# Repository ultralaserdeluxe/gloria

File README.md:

gloria
======

TSEA29: Lagerrobot

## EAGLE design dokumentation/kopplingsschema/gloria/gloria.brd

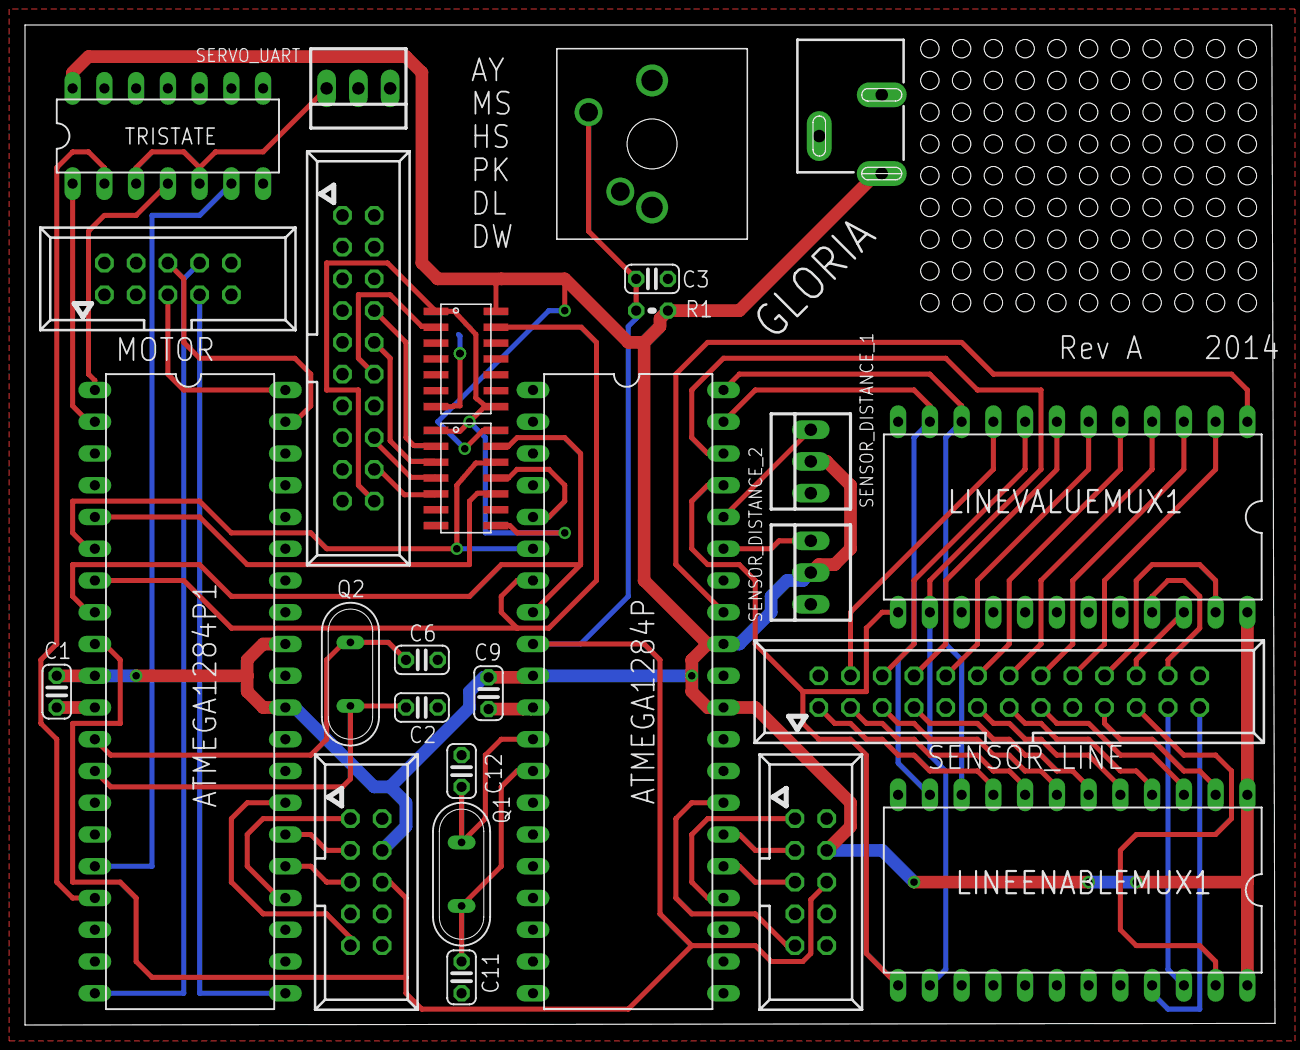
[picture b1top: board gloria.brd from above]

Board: 2 copper layers, 100.0 x 80.0 mm, 36 parts (0 on the bottom side), 64 nets.

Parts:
ATMEGA1284P: SENSOR UNIT; DIL40
ATMEGA1284P1: DRIVE UNIT; DIL40
C1, C3, C9: 100n; C025-024X044
C2, C6, C11, C12: 22p; C025-024X044
JP1: POWER_JACKSLT; POWER_JACK_SLOT
JP26, JP27, JP28, JP29, JP30, JP31, JP32, JP33, JP34: M11POGOPIN_HOLES_ONLY; 1X11_HOLES_ONLY
JTAG_SEN: 057-010-1
JTAG_STYR: 057-010-1
LINEENABLEMUX1: 4067N; DIL24-6
LINEVALUEMUX1: 4067N; DIL24-6
MOTOR: 057-010-1
Q1, Q2: 16M; QS
R1: 10k; 0204V
SENSOR_DISTANCE_1, SENSOR_DISTANCE_2: 22-23-2031
SENSOR_LINE: 057-026-1
SERVO_UART: 22-23-2031
TRISTATE: 74LS125N; DIL14
U$1, U$2: TXB0104SOIC(D); TXB0104
U$6: CHERRY-MX-I
X: 057-020-1

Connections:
DISTANCELEFT: ATMEGA1284P.36, SENSOR_DISTANCE_1.3
GND: ATMEGA1284P.11, ATMEGA1284P.31, ATMEGA1284P1.11, ATMEGA1284P1.31, C1.1, C2.1, C3.1, C6.1, C9.1, C11.1, C12.1, JP1.GND@1, JP1.GND@2, JTAG_SEN.2, JTAG_SEN.10, JTAG_STYR.2, JTAG_STYR.10, LINEENABLEMUX1.12, LINEENABLEMUX1.15, LINEVALUEMUX1.12, LINEVALUEMUX1.15, MOTOR.1, SENSOR_DISTANCE_1.1, SENSOR_DISTANCE_2.1, SENSOR_LINE.2, SENSOR_LINE.9, SENSOR_LINE.17, SENSOR_LINE.26, SERVO_UART.1, TRISTATE.7, U$1.P$7, U$2.P$7, U$6.PIN-1, X.2
LINEADDR0: ATMEGA1284P.40, LINEENABLEMUX1.10, LINEVALUEMUX1.10
LINEADDR1: ATMEGA1284P.39, LINEENABLEMUX1.11, LINEVALUEMUX1.11
LINEADDR2: ATMEGA1284P.38, LINEENABLEMUX1.14, LINEVALUEMUX1.14
LINEADDR3: ATMEGA1284P.37, LINEENABLEMUX1.13, LINEVALUEMUX1.13
LINEVALUE: ATMEGA1284P.33, LINEVALUEMUX1.1
MISO: ATMEGA1284P.7, ATMEGA1284P1.7, U$2.P$13
MOSI: ATMEGA1284P.6, ATMEGA1284P1.6, U$1.P$12
unnamed: ATMEGA1284P.27, JTAG_SEN.9
unnamed: ATMEGA1284P1.24, JTAG_STYR.1
unnamed: ATMEGA1284P.26, JTAG_SEN.3
unnamed: ATMEGA1284P.25, JTAG_SEN.5
unnamed: ATMEGA1284P.24, JTAG_SEN.1
unnamed: ATMEGA1284P1.27, JTAG_STYR.9
unnamed: ATMEGA1284P1.26, JTAG_STYR.3
unnamed: ATMEGA1284P1.25, JTAG_STYR.5
unnamed: ATMEGA1284P1.21, MOTOR.7
unnamed: LINEENABLEMUX1.9, SENSOR_LINE.1
unnamed: LINEENABLEMUX1.8, SENSOR_LINE.3
unnamed: LINEENABLEMUX1.7, SENSOR_LINE.5
unnamed: LINEENABLEMUX1.6, SENSOR_LINE.7
unnamed: LINEENABLEMUX1.5, SENSOR_LINE.11
unnamed: LINEENABLEMUX1.4, SENSOR_LINE.13
unnamed: LINEENABLEMUX1.3, SENSOR_LINE.15
unnamed: LINEENABLEMUX1.2, SENSOR_LINE.19
unnamed: LINEENABLEMUX1.23, SENSOR_LINE.21
unnamed: LINEENABLEMUX1.22, SENSOR_LINE.23
unnamed: LINEENABLEMUX1.21, SENSOR_LINE.25
unnamed: LINEVALUEMUX1.9, SENSOR_LINE.4
unnamed: LINEVALUEMUX1.8, SENSOR_LINE.6
unnamed: LINEVALUEMUX1.7, SENSOR_LINE.8
unnamed: LINEVALUEMUX1.6, SENSOR_LINE.10
unnamed: LINEVALUEMUX1.5, SENSOR_LINE.12
unnamed: LINEVALUEMUX1.4, SENSOR_LINE.14
unnamed: LINEVALUEMUX1.3, SENSOR_LINE.16
unnamed: LINEVALUEMUX1.2, SENSOR_LINE.18
unnamed: LINEVALUEMUX1.23, SENSOR_LINE.20
unnamed: LINEVALUEMUX1.22, SENSOR_LINE.22
unnamed: LINEVALUEMUX1.21, SENSOR_LINE.24
unnamed: ATMEGA1284P.35, SENSOR_DISTANCE_2.3
unnamed: U$1.P$1, U$1.P$8, U$2.P$1, U$2.P$8, X.20
unnamed: ATMEGA1284P1.40, MOTOR.5
unnamed: U$1.P$2, X.8
unnamed: U$1.P$3, X.10
unnamed: U$2.P$2, X.12
unnamed: U$1.P$4, X.16
unnamed: U$1.P$5, X.18
unnamed: ATMEGA1284P1.39, MOTOR.6
unnamed: ATMEGA1284P.12, C12.2, Q1.2
unnamed: ATMEGA1284P1.20, MOTOR.8
unnamed: ATMEGA1284P.13, C11.2, Q1.1
unnamed: ATMEGA1284P1.12, C6.2, Q2.2
unnamed: ATMEGA1284P1.13, C2.2, Q2.1
RESET: ATMEGA1284P.9, ATMEGA1284P1.9, C3.2, JTAG_SEN.6, JTAG_STYR.6, R1.1, U$6.PIN-2
SCK: ATMEGA1284P.8, ATMEGA1284P1.8, U$1.P$13
SERVOUART: SERVO_UART.3, TRISTATE.3, TRISTATE.5
SS0: ATMEGA1284P1.5, U$1.P$10
SS1: ATMEGA1284P.5, U$1.P$11
STYR_UART_RX_E: ATMEGA1284P1.1, TRISTATE.4
STYR_UART_TX_E: ATMEGA1284P1.2, TRISTATE.1
UART1RX: ATMEGA1284P1.16, TRISTATE.6
UART1TX: ATMEGA1284P1.17, TRISTATE.2
VCC: ATMEGA1284P.10, ATMEGA1284P.30, ATMEGA1284P.32, ATMEGA1284P1.10, ATMEGA1284P1.30, ATMEGA1284P1.32, C1.2, C9.2, JP1.PWR, JTAG_SEN.4, JTAG_STYR.4, LINEENABLEMUX1.1, LINEENABLEMUX1.24, LINEVALUEMUX1.24, R1.2, SENSOR_DISTANCE_1.2, SENSOR_DISTANCE_2.2, TRISTATE.14, U$1.P$14, U$2.P$14

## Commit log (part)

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2014-10-29 Modified is_on_straight.
2014-10-29 Fixed distance values
2014-10-29 Changed regulator behaviour when on crossings or breaks.
2014-10-29 Fixed station_center on crossings/breaks.
2014-10-29 Added setAll function.
2014-10-29 Changed station front for the better and the lower/upper limits.
2014-10-29 Changed stuff.
2014-10-29 driveUnit can now handle float in motor speeds.
2014-10-29 pcThread can now work with the shared stuff dictionary.
2014-10-29 Lots of changes.
2014-10-29 Changed station functions to a class and made it incorporate past values in desicions.
2014-10-29 Added hasPackage functionality.
2014-10-29 Fixed regulator.
2014-10-29 Fixed stop stations.
2014-10-29 stopstations works
2014-11-03 Fixed broken file.
2014-11-03 Designspec updated to v1.0(unconfirmed)
2014-11-03 uppdaterat statusrapporten
2014-11-04 gitignore updated w Atmes Studio, styrenhet src initiated
2014-11-04 uppdaterat datum i statusrapport
2014-11-06 gitignore updated, initiated src styrenhet and sensorenhet
2014-11-06 Kodstandard added
2014-11-06 Added a file for SPI functions.
2014-11-06 Created a simple echo test with SPI interrupts.
2014-11-07 Protokoll möte 20141105 updated
2014-11-07 Added PythonModule for PC and DAD
2014-11-08 Built data-types and queue for styrenhet
2014-11-09 Styrenhet now builds
2014-11-09 Added ISR to spi functions.
2014-11-09 Styrenhet partially updated
2014-11-09 Implemented transmission for SPI slave, untested
2014-11-10 Testing PWM.
2014-11-10 Removed bogus comments
2014-11-10 Mötesprotokoll 20141110 added
2014-11-11 Removed bogus comments from PCmodule
2014-11-11 kopplingsschema updated
2014-11-11 Update gitignore w eagle
2014-11-12 PCGUI stub
2014-11-12 Test textfile added
2014-11-12 Experimenting with .txt file command sending
2014-11-12 Working GUI for motor handling!
2014-11-12 loleagle
2014-11-12 wrote a new pc-dad communication module
2014-11-13 added styrlogik
2014-11-13 Improved performance sensorenhet
2014-11-14 Fixed usart.
2014-11-14 Test of controlling servii.
2014-11-14 Added functions for working with sensors.
2014-11-14 Updated sensor unit to use the new sensor functions.
2014-11-15 Restructured and updated styrenhet. SPI not implemented.
2014-11-15 some stuff changed in styrlogik
2014-11-15 moved styrlogik to martins
2014-11-15 Styrmodul hopefully has functional datatypes
2014-11-15 Added Mötesprotokoll 20141115
2014-11-16 Changed spi functions to not use the transmit queue.
2014-11-16 Fixed uninitialised pointer.
2014-11-16 Added working spi recieve handler and updated main loop.
2014-11-16 Styrenhet now acts based on streams of data
2014-11-17 new module for sensorreading
2014-11-17 Various updates
2014-11-18 flyttade mainthreadtill styrlogik, började på kalibreringsfunktionen
2014-11-18 wrote an arm class
2014-11-19 kalibrering klar? började på styrbibliotek för maintråden
2014-11-19 Styrenhet updated. Theres code to fix memoryleak (gets stuck in loop) and updated servo_init (still not working properly)
2014-11-20 Cleaned folder of unusable files, made copy, cont. GUI
2014-11-20 Added GUI input for ARM, working on autoarm/motor, also status/calibrate
2014-11-20 Fully working GUI for old version
2014-11-20 la till lite grejjer i driveunit å i maintraden
2014-11-20 updated statusrapport
2014-11-20 new joystick class and a testprogram to controll motors with joystick
2014-11-21 Cleaned naming errors of modules, SPI module missing, where is it?
2014-11-21 removed martin folder
2014-11-21 moved some python files around, everything for the pc is under PC and everything for the mainunit is under huvudenhet
2014-11-21 added some missing files in styrlogik
2014-11-21 changed beaglemain
2014-11-21 Mötesprotokoll 20141121 added
2014-11-21 Added motor control.
2014-11-21 fixed checksubelement so it handles float
2014-11-21 Fixed motor control.
2014-11-22 fixed pcModule with package tail handling
2014-11-22 Updated circuit diagram.
2014-11-23 Various changes
2014-11-23 Fixed a few input bugs resulting in nonexisting values
2014-11-23 Updated circuit diagrams.
2014-11-23 Updated circuit diagrams some more.
2014-11-24 tata57
2014-11-24 Added protokoll 20141124
2014-11-24 changed comments to english
2014-11-24 Styrenheten are now capable of doing stuff on command
2014-11-24 Began work on usart timeout
2014-11-25 Changed keybind implementation to a more driving feel, now uses speed variable for acceleration/deacceleration
2014-11-25 Connected uninvoked pins.
2014-11-25 A few bugfixes to speed input and variable change, hardcaped -100 <= speed <= 100
2014-11-25 USART_recieve now timeouts if no recieved msg
2014-11-25 Added prototyping area.
2014-11-26 Fixed motors initial velocity (untested)
2014-11-27 Complementary commit
2014-11-27 added package detection test
2014-11-27 regulator to regulate
2014-11-27 recover lost sensorthread file
2014-11-27 a test for the regulator
2014-11-27 script for connection to bb
2014-11-28 improved regulator
2014-11-28 Rerouted board manually.
2014-11-28 Mötesprotokoll 20141128 added
2014-11-29 Removed acceleration from motor
2014-11-29 Added some erfarenhet
2014-11-30 Added skeleton for efterstudie
2014-11-30 Added skeleton for tekdok
2014-12-01 Fixed a memoryleak. Theres still a timing-error (i think) somewhere
2014-12-01 Statusrapport 20141201 added
2014-12-02 Mötesprotokoll 20141201 added
2014-12-02 Everything is done in interrupt. Needs testing
2014-12-02 Extracted parameter_chain from servo
2014-12-02 Replaced old with new
2014-12-02 Started rebuilding regulator.
2014-12-02 TATA57 is now on Google Drive.
2014-12-02 Added script to find IP of BB.
2014-12-02 Moved new regulator to suitable place.
2014-12-02 Updated gitignore.
2014-12-02 Removed .pyc files.
2014-12-02 mainthread ready for testing
2014-12-02 Cleaning repo: Replaced old PCGUI with correct one
2014-12-02 Moved arm.py to suitable place.
2014-12-02 Renamed sensorenhet.
2014-12-02 Added encoding of sendData
2014-12-02 Renamed huvudenhet.
2014-12-02 Renamed styrenhet.
2014-12-02 Added encoding/decoding of data in appropriate places
2014-12-02 Added one important comment line (27) just to be sure
2014-12-02 Moved styrlogik files to a suitable place.
2014-12-02 Moved file.
2014-12-02 Deleted old regulator.
2014-12-02 Removed old test file and renamed regulatorNew.
2014-12-02 Fixing mainThread.
2014-12-02 Added a decode and fixed a minor error.
2014-12-03 Added ignored file
2014-12-03 Changed the placement of Teori in tekdok
2014-12-03 For got about SPI in gitignore
2014-12-03 Now ready for testing
2014-12-03 Changed to old regulator class but changed position calculations.
2014-12-03 Connection script now accepts ip-address as argument.
2014-12-03 added stopstationdetection function
2014-12-03 Made connect bash script more potent
2014-12-03 Fixed minor bug in connect.sh
2014-12-03 Updated tekdok
2014-12-04 Fixed PWM, can now run at much slower speed
2014-12-04 Fixed bug with local variables
2014-12-04 If expect is installed, connect will also provide ssh password
2014-12-04 Minor changes
2014-12-04 some changes in mainThread
2014-12-05 remade arm module
2014-12-05 added comment about arm limits in pcModule
2014-12-05 Mötesprotokoll 20141205 added
2014-12-05 Added spi_dummy file for testing on platforms other than Beagleboard.
2014-12-06 mainThread now uses dictionary instead of sensorList.
2014-12-06 Renamed regulatorNew -> regulator.
2014-12-06 Commiting uncommited files from master branch on BB.
2014-12-07 minor changes in mainThread
2014-12-07 Added IP argument (no error checking) to PCGUI
2014-12-07 Tekdok: Did some general editing, added some graphics, moved files into dirs
2014-12-07 Fixed small bug.
2014-12-08 fixed int/float problem
2014-12-08 Mötesprotokoll 20141208 added
2014-12-08 Changed turnleft and turnright to use SPIN (-speed/speed, speed/-speed), Q,E now spins at max speed
2014-12-08 Kravspec updated to v1.1
2014-12-08 Initiated Användarhandledning
2014-12-08 Restructured tex-dirs
2014-12-08 Massive layout changes. Added support for status in the GUI. A few tweaks on layout of previous buttons.
2014-12-08 Patched dates on front page
2014-12-08 Fixed minor errors.
2014-12-08 Adde BOM.
2014-12-08 Fixed stuff.
2014-12-09 Small value display fixes
2014-12-09 Usart interrupt-driven, servo status updated only on command. Might still crash on status-command
2014-12-09 Dokumentation now follows a naming scheme
2014-12-10 Moved files to right directory
2014-12-10 Arm and motor now global variables in arm.h/motor.h
2014-12-10 Merged usart
2014-12-10 Extracted functionality from read_command to separate functions
2014-12-10 Motor now without interrupt/acceleration
2014-12-11 Sensorunit updated to work with additional line sensors
2014-12-11 added pictures
2014-12-11 .eps graphic files in documentation are no longer ignored
2014-12-11 Some formatting
2014-12-11 Fixed bug with wrong address in case
2014-12-11 set timeout for the connect in pcModule
2014-12-11 Progress.
2014-12-11 Keep the streak alive\!
2014-12-12 added halt command to pcmodule
2014-12-12 Tekdok updated
2014-12-12 new gui
2014-12-12 Fixed broken motesprotokoll
2014-12-12 Changed sensorThreads access to calibration data.
2014-12-12 Added calibration functionality.
2014-12-12 Gui can now be started without joystick.
2014-12-12 Fixed possible zero division errors.
2014-12-12 better gui
2014-12-13 Added calibration and normalization of middle sensors.
2014-12-13 Added lots of logic.
2014-12-13 Minor updates
2014-12-13 modified regulator, works somewhat better
2014-12-13 gui show height
2014-12-13 changed regulator and added filtered value for distance sensors NOT TESTED
2014-12-13 removed print
2014-12-13 can control wrist angle,rotation and grip
2014-12-13 Added new is_on_straight function.
2014-12-13 Fixed typo
2014-12-13 Renamed sensor_eval
2014-12-13 Added conditional regulation
2014-12-13 Fixed typos.
2014-12-14 Added picture, few changes in lines, missing Gripklo and final touch
2014-12-14 updated Gui name
2014-12-15 Updated picture to something more serious
2014-12-15 Renamed panel name to something not including the word fuck
2014-12-15 motesprotokoll 2041215 added
2014-12-15 Increased max speed in manual mode.
2014-12-15 Last fixes to fonts, removed todo:s, subsectionized styrning, corrected gripklo-steering (ONLY missing up/down now), added figure to Gui.png
2014-12-15 Renames, edits to steering manual, added short intro. One bug with pagebreak after Styrning, appendix refuses to pagebreak?
2014-12-15 Added explanations to system (ansluta), fixed a page numbering error
2014-12-15 updated kopplingsschema
2014-12-15 Added 3rd subsection for styr (calibrate), added short about AVR, finalized picture, fixed some unnecessary pagebreaks
2014-12-15 added text to PC-enheten
2014-12-15 Fixed a seriously annoying bug.
2014-12-15 Fixed bug in sensorunit
2014-12-16 added slutsatser to tekdok
2014-12-16 fixed kopplingsschema in tekdok
2014-12-16 Added flush timer to mainthread
2014-12-16 corrected typos
2014-12-16 Flush is now new and improved.
2014-12-16 better stuff
2014-12-16 corrected some sentences
2014-12-16 Fixed regulator in tekdok
2014-12-16 Tekdok updated to v0.1
2014-12-16 Uploaded v0.1 and v1.0 of anvandarhandledning
2014-12-16 Tekdok now v1.0
2014-12-16 Fixed command_queue
2014-12-16 fixed some rounding off erros
2014-12-16 arm controls just sends increase in position
2014-12-16 average joystick
2014-12-16 Added out of bounds function.
2014-12-16 Added stuff.
2014-12-16 Hack the Gibson.
2014-12-16 Patch the gibson.
2014-12-16 beter
2014-12-17 fixed gui arm joystick
2014-12-17 changed freq in gui
2014-12-17 changed values in gui'
2014-12-17 Corrected graph for sensorvalues
2014-12-17 Added calibrat.
2014-12-17 fixed some with the new sensordistance values
2014-12-17 Returns to default position upon startup
2014-12-17 Better carry pos values.
2014-12-17 More fitting delays in fixed arm positions
2014-12-17 Changed distance values to 15.
2014-12-19 Added picture as requested by Tomas. Edited Subsequent picture info to fit with the new change of order.
2014-12-19 Prettied up pagebreaking aswell.
2014-12-22 Tekdok and anvh updated to v1.1. layout can now contain picture on frontpage

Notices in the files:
parts and their libraries:
SparkFun-Connectors: Licensing: Creative Commons ShareAlike 4.0 International - https://creativecommons.org/licenses/by-sa/4.0
